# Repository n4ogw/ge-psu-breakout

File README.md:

# ge-psu-breakout
Breakout board for GE CP3000 power supply. The main connector is an Amphenol
FCI 51762-10402400ABLF.

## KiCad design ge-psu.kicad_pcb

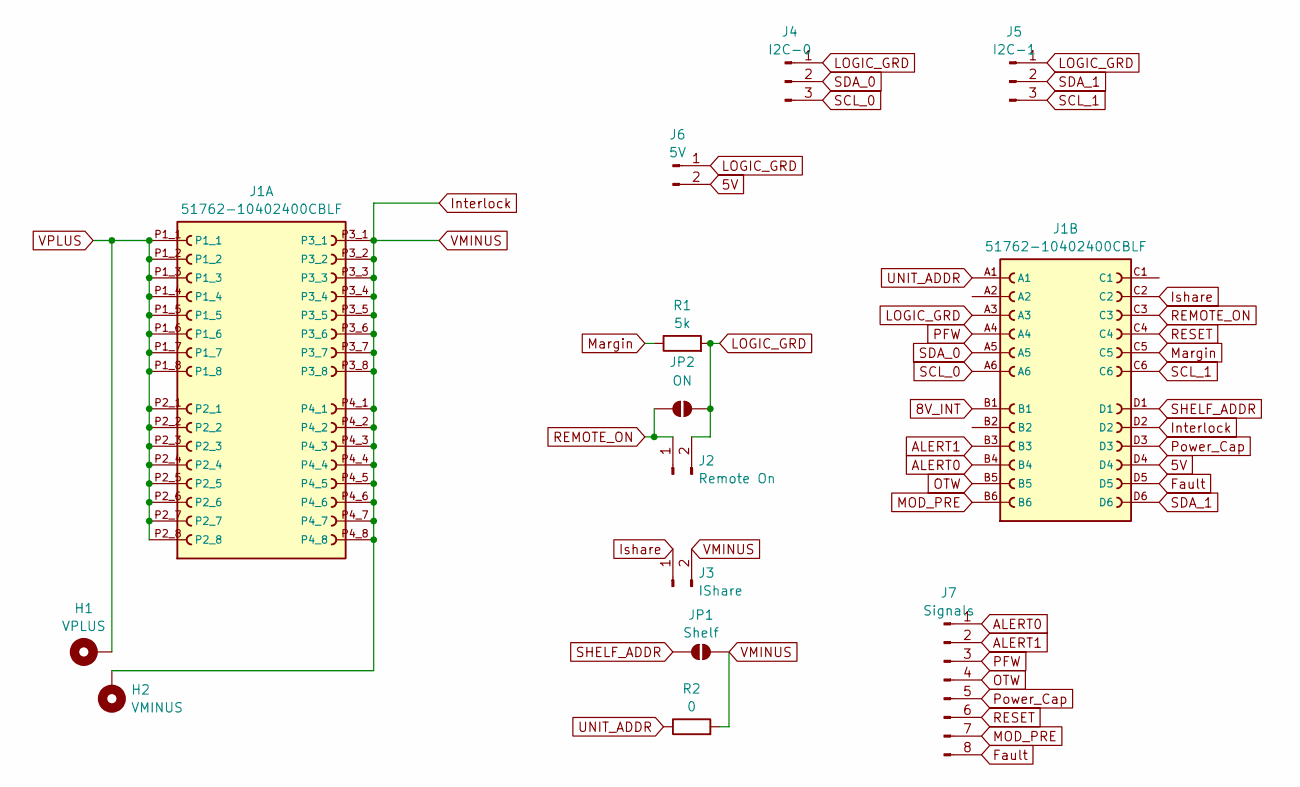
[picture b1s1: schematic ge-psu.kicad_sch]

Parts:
H1: VPLUS; MountingHole_6.5mm_Pad_Via
H2: VMINUS; MountingHole_6.5mm_Pad_Via
J1: 51762-10402400CBLF; AMPHENOL_51762-10402400CBLF; PARTREV K
J2: Remote On; PinHeader_1x02_P2.54mm_Vertical
J3: IShare; PinHeader_1x02_P2.54mm_Vertical
J4: I2C-0; PinHeader_1x03_P2.54mm_Vertical
J5: I2C-1; PinHeader_1x03_P2.54mm_Vertical
J6: 5V; PinHeader_1x02_P2.54mm_Vertical
J7: Signals; PinHeader_1x08_P2.54mm_Vertical
JP1: Shelf; SolderJumper-2_P1.3mm_Open_Pad1.0x1.5mm
JP2: ON; SolderJumper-2_P1.3mm_Open_Pad1.0x1.5mm
R1: 5k; R_0805_2012Metric_Pad1.20x1.40mm_HandSolder
R2: 0; R_0805_2012Metric_Pad1.20x1.40mm_HandSolder

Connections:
5V: J1.D4, J6.2
8V_INT: J1.B1
ALERT0: J1.B4, J7.1
ALERT1: J1.B3, J7.2
Fault: J1.D5, J7.8
Interlock: H2.1, J1.D2, J1.P3_1, J1.P3_2, J1.P3_3, J1.P3_4, J1.P3_5, J1.P3_6, J1.P3_7, J1.P3_8, J1.P4_1, J1.P4_2, J1.P4_3, J1.P4_4, J1.P4_5, J1.P4_6, J1.P4_7, J1.P4_8, J3.2, JP1.2 (B), R2.2
Ishare: J1.C2, J3.1
LOGIC_GRD: J1.A3, J2.2, J4.1, J5.1, J6.1, JP2.2 (B), R1.2
MOD_PRE: J1.B6, J7.7
Margin: J1.C5, R1.1
OTW: J1.B5, J7.4
PFW: J1.A4, J7.3
Power_Cap: J1.D3, J7.5
REMOTE_ON: J1.C3, J2.1, JP2.1 (A)
RESET: J1.C4, J7.6
SCL_0: J1.A6, J4.3
SCL_1: J1.C6, J5.3
SDA_0: J1.A5, J4.2
SDA_1: J1.D6, J5.2
SHELF_ADDR: J1.D1, JP1.1 (A)
UNIT_ADDR: J1.A1, R2.1
VPLUS: H1.1, J1.P1_1, J1.P1_2, J1.P1_3, J1.P1_4, J1.P1_5, J1.P1_6, J1.P1_7, J1.P1_8, J1.P2_1, J1.P2_2, J1.P2_3, J1.P2_4, J1.P2_5, J1.P2_6, J1.P2_7, J1.P2_8

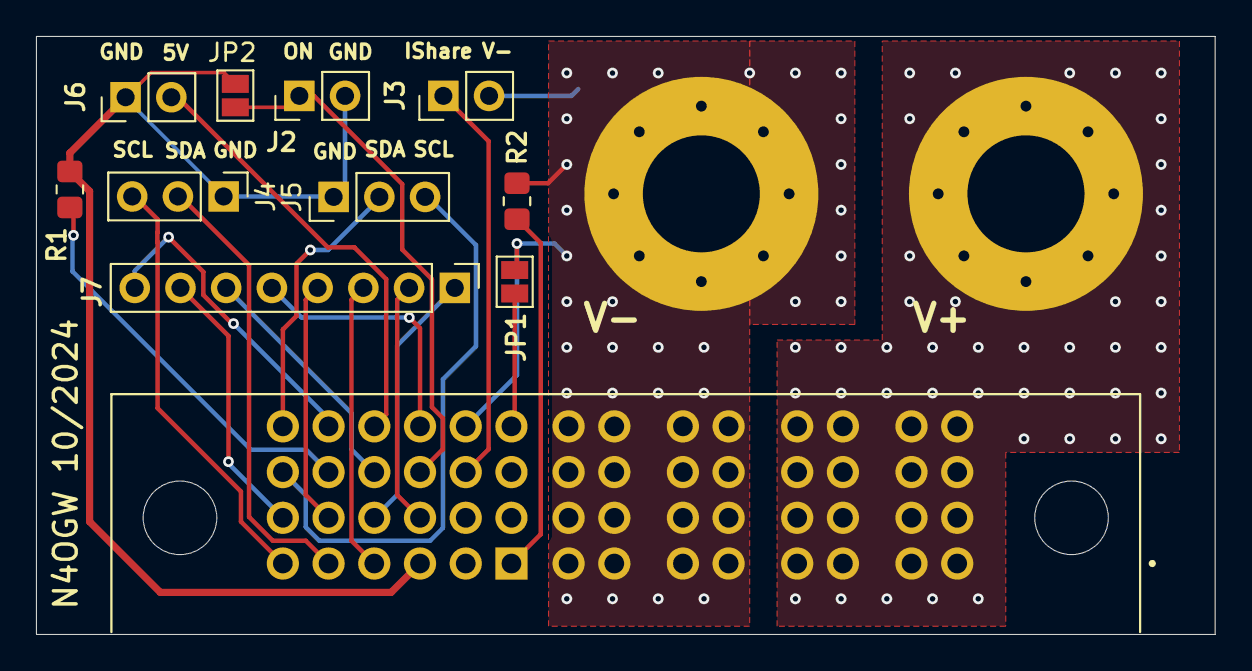
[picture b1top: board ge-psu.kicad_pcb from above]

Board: 2 copper layers, 65.5 x 33.2 mm, 13 parts (0 on the bottom side), 21 nets.
